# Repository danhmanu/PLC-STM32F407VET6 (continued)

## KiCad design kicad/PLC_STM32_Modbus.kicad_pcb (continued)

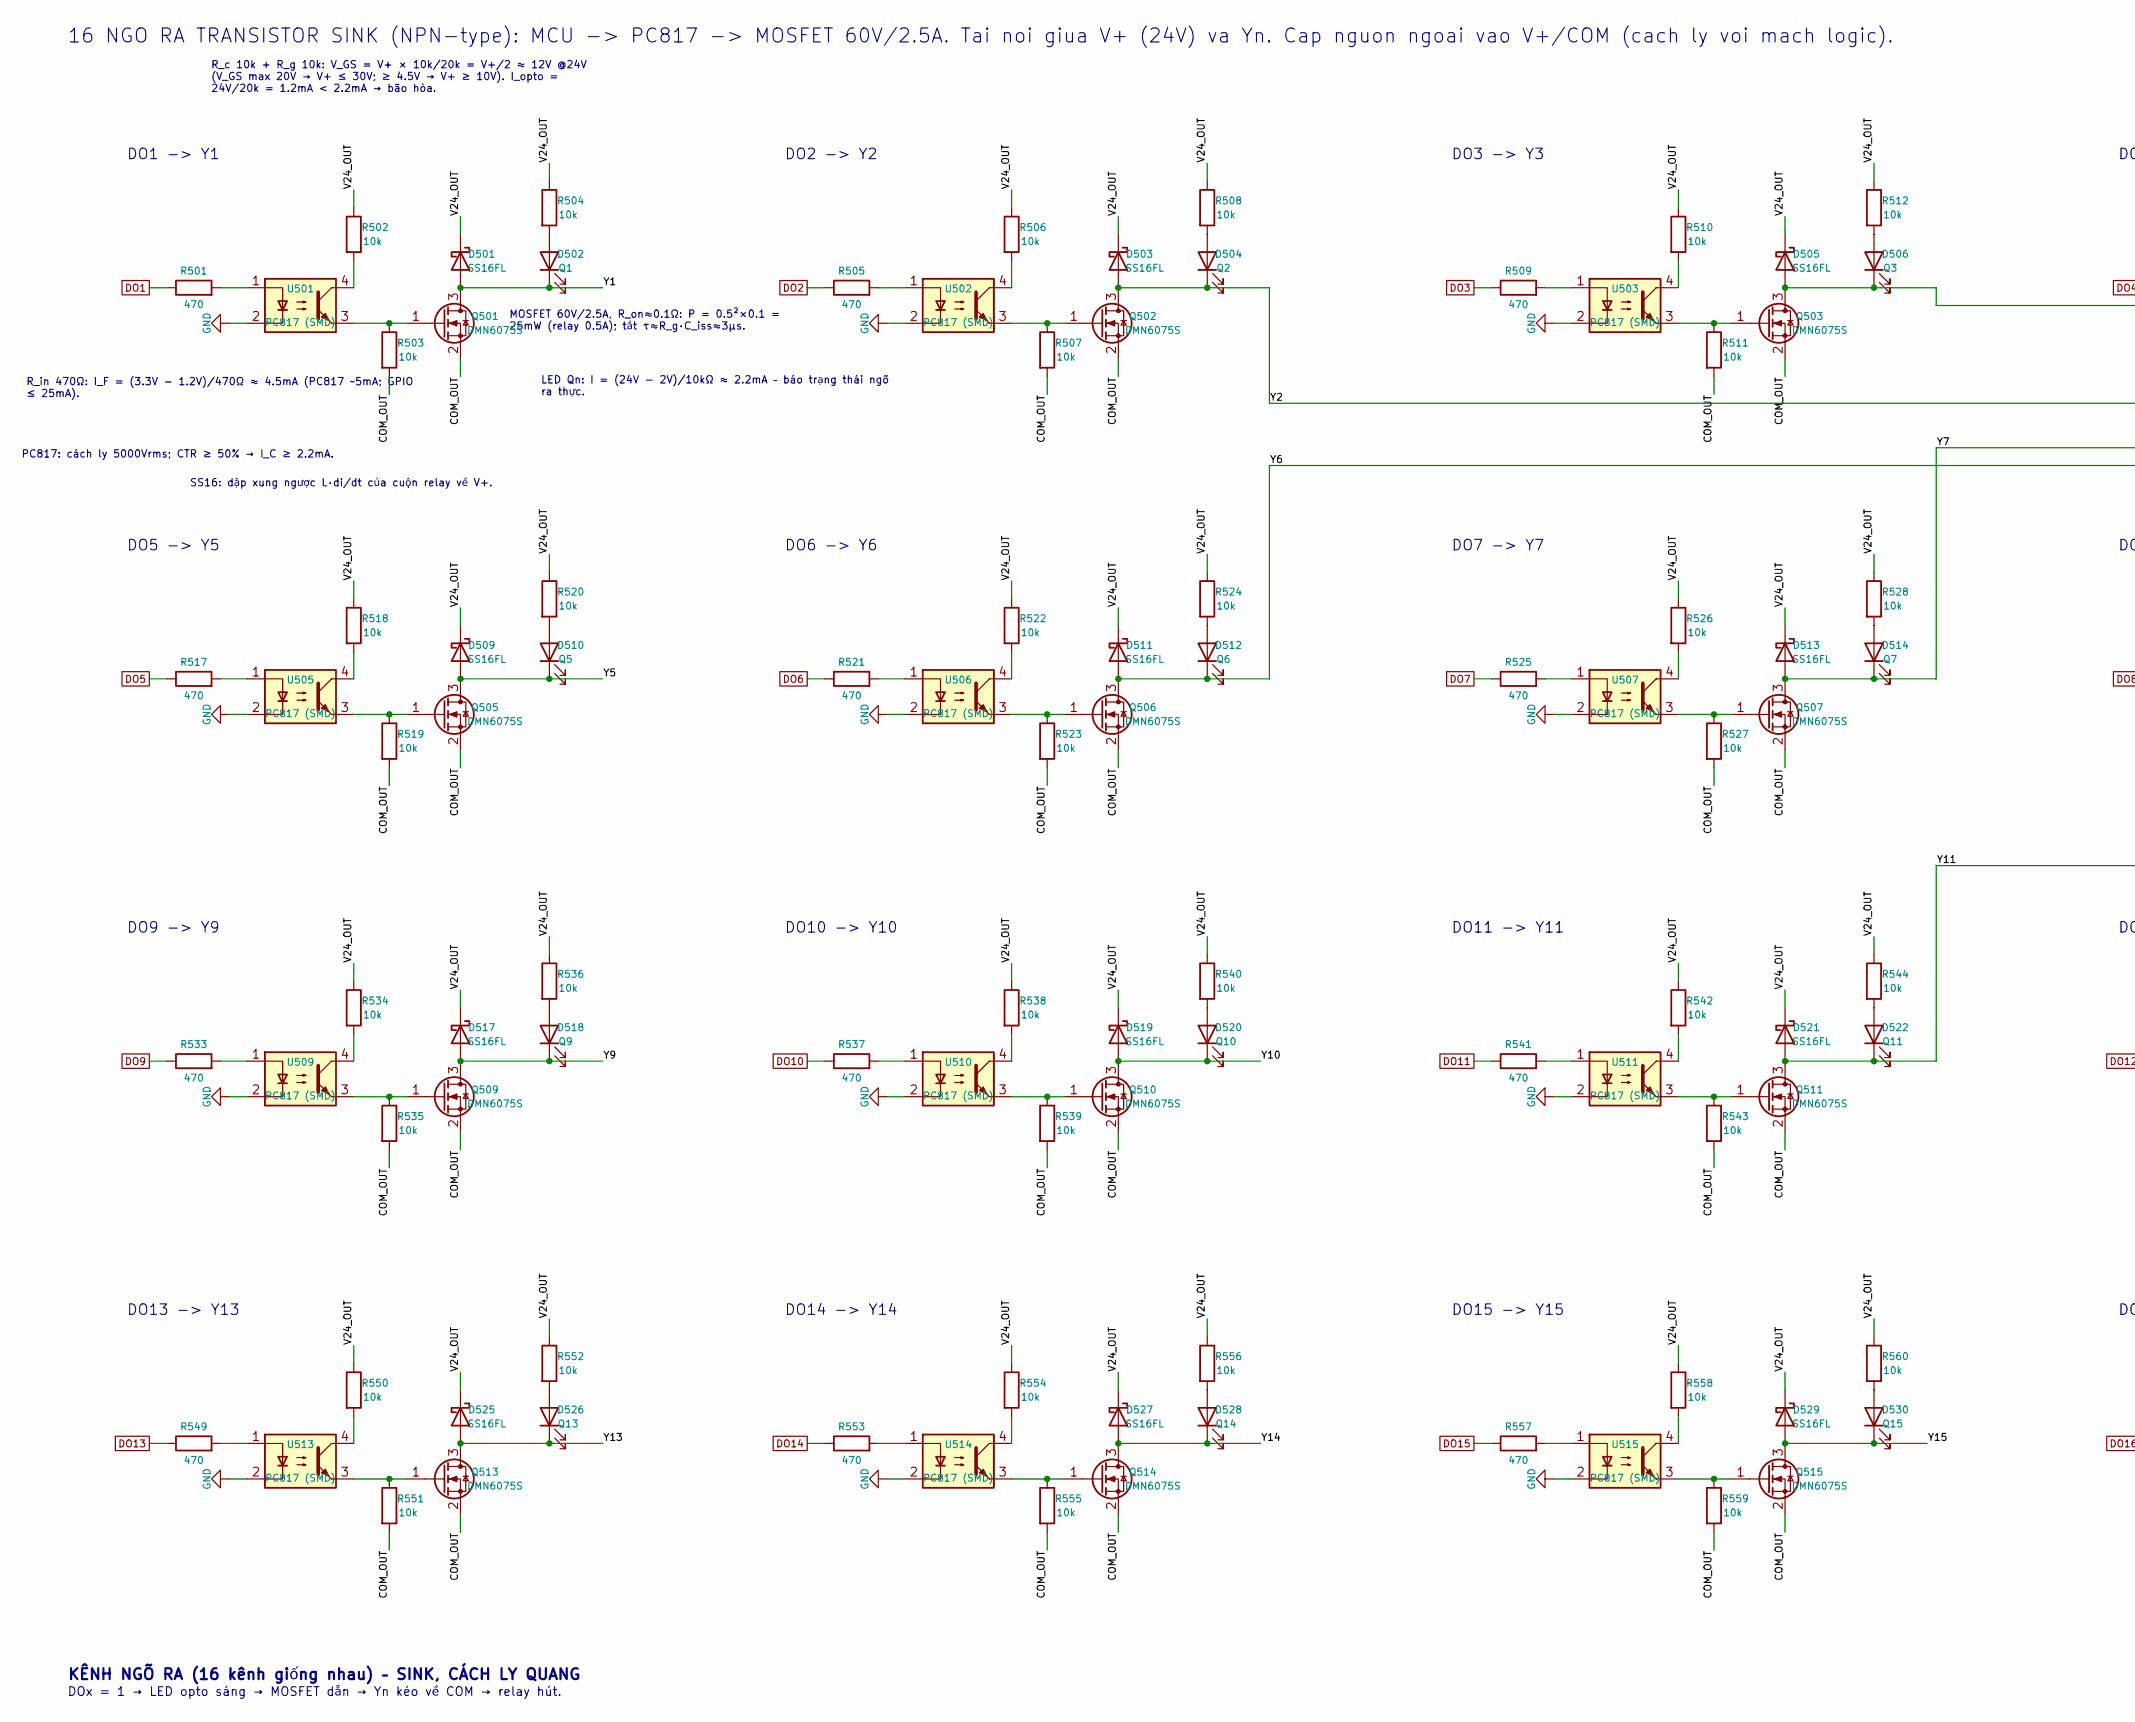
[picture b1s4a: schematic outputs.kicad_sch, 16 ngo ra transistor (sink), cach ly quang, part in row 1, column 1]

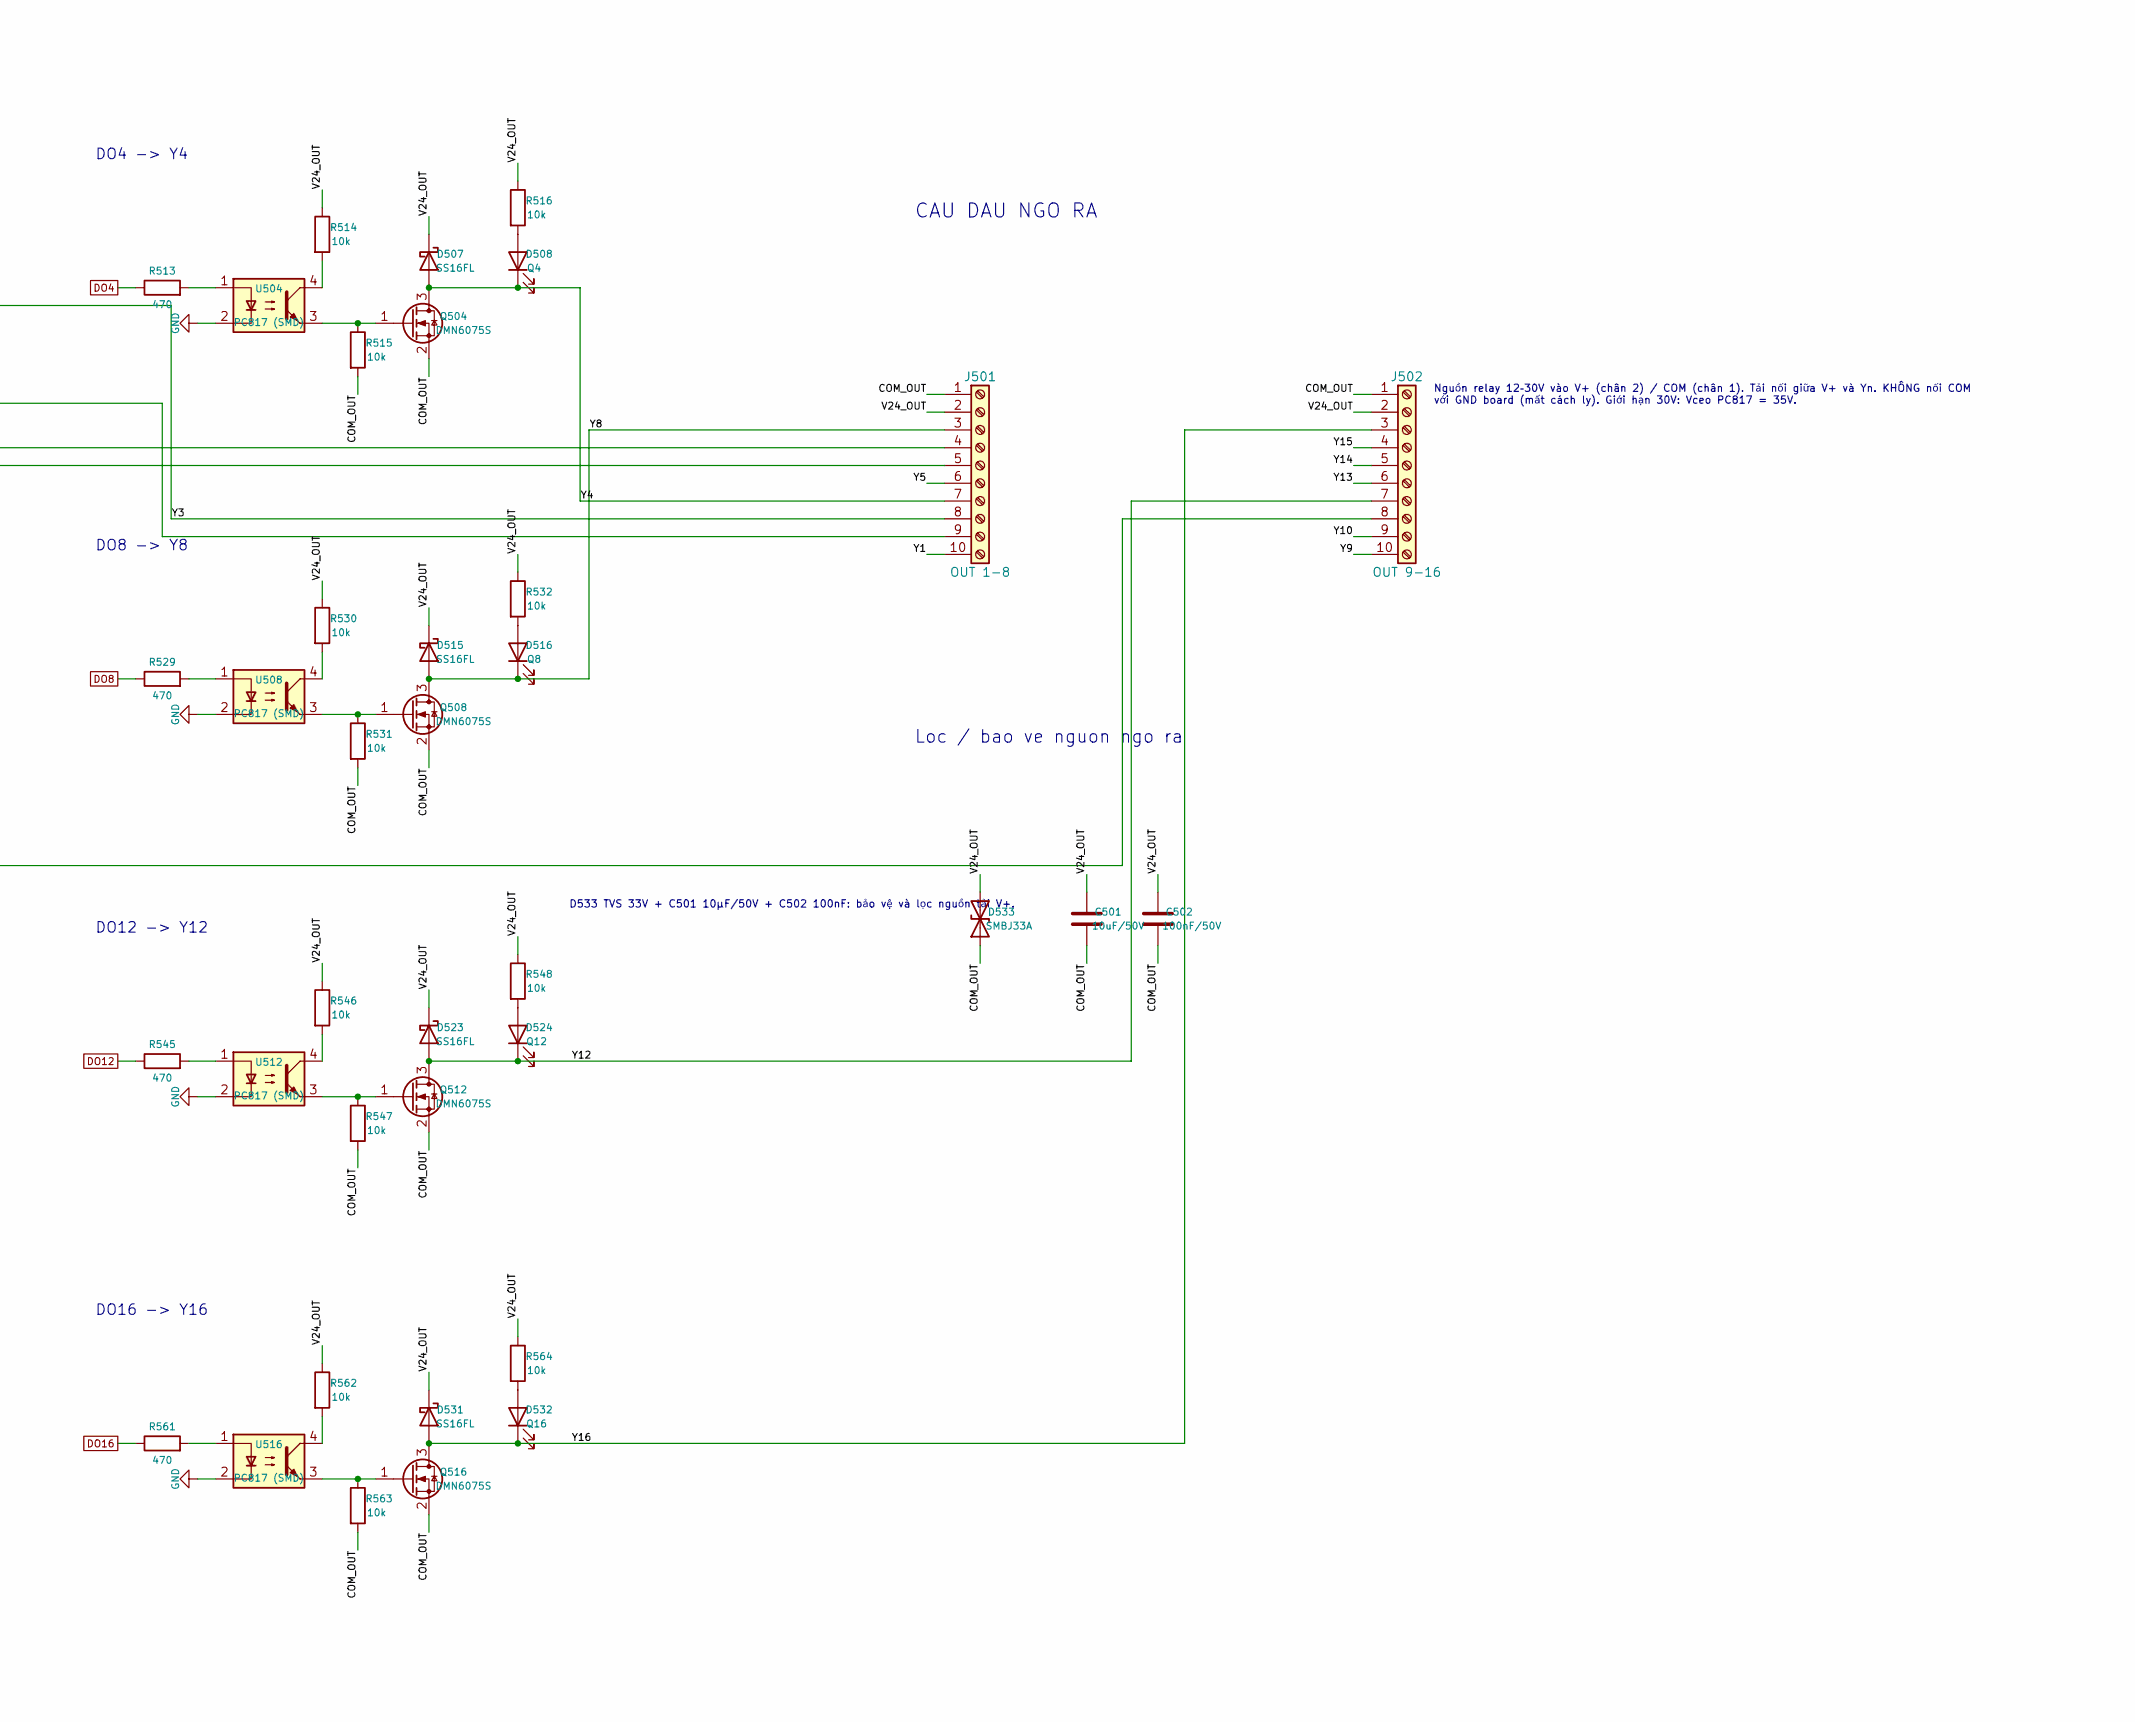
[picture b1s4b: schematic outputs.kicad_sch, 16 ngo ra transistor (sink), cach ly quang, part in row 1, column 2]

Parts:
C501: 10uF/50V; C_1206_3216Metric
C502: 100nF/50V; C_0805_2012Metric
D501, D503, D505, D507, D509, D511, D513, D515, D517, D519, D521, D523, D525, D527, D529, D531: SS16FL; D_SOD-123F
D502: Q1; LED_0603_1608Metric
D504: Q2; LED_0603_1608Metric
D506: Q3; LED_0603_1608Metric
D508: Q4; LED_0603_1608Metric
D510: Q5; LED_0603_1608Metric
D512: Q6; LED_0603_1608Metric
D514: Q7; LED_0603_1608Metric
D516: Q8; LED_0603_1608Metric
D518: Q9; LED_0603_1608Metric
D520: Q10; LED_0603_1608Metric
D522: Q11; LED_0603_1608Metric
D524: Q12; LED_0603_1608Metric
D526: Q13; LED_0603_1608Metric
D528: Q14; LED_0603_1608Metric
D530: Q15; LED_0603_1608Metric
D532: Q16; LED_0603_1608Metric
D533: SMBJ33A; D_SMB
J501: OUT 1-8; TerminalBlock_Phoenix_MKDS-1-10-3.81_1x10_P3.81mm_Horizontal
J502: OUT 9-16; TerminalBlock_Phoenix_MKDS-1-10-3.81_1x10_P3.81mm_Horizontal
Q501, Q502, Q503, Q504, Q505, Q506, Q507, Q508, Q509, Q510, Q511, Q512, Q513, Q514, Q515, Q516: DMN6075S; SOT-23
R501, R505, R509, R513, R517, R521, R525, R529, R533, R537, R541, R545, R549, R553, R557, R561: 470; R_0603_1608Metric
R502, R503, R504, R506, R507, R508, R510, R511, R512, R514, R515, R516, R518, R519, R520, R522, R523, R524, R526, R527, R528, R530, R531, R532, R534, R535, R536, R538, R539, R540, R542, R543, R544, R546, R547, R548, R550, R551, R552, R554, R555, R556, R558, R559, R560, R562, R563, R564: 10k; R_0603_1608Metric
U501, U502, U503, U504, U505, U506, U507, U508, U509, U510, U511, U512, U513, U514, U515, U516: PC817 (SMD); SMDIP-4_W9.53mm

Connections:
/16 ngo ra transistor/COM_OUT: C501.2, C502.2, D533.1 (A1), J501.1, J502.1, Q501.2 (S), Q502.2 (S), Q503.2 (S), Q504.2 (S), Q505.2 (S), Q506.2 (S), Q507.2 (S), Q508.2 (S), Q509.2 (S), Q510.2 (S), Q511.2 (S), Q512.2 (S), Q513.2 (S), Q514.2 (S), Q515.2 (S), Q516.2 (S), R503.2, R507.2, R511.2, R515.2, R519.2, R523.2, R527.2, R531.2, R535.2, R539.2, R543.2, R547.2, R551.2, R555.2, R559.2, R563.2
/16 ngo ra transistor/V24_OUT: C501.1, C502.1, D501.1 (K), D503.1 (K), D505.1 (K), D507.1 (K), D509.1 (K), D511.1 (K), D513.1 (K), D515.1 (K), D517.1 (K), D519.1 (K), D521.1 (K), D523.1 (K), D525.1 (K), D527.1 (K), D529.1 (K), D531.1 (K), D533.2 (A2), J501.2, J502.2, R502.1, R504.1, R506.1, R508.1, R510.1, R512.1, R514.1, R516.1, R518.1, R520.1, R522.1, R524.1, R526.1, R528.1, R530.1, R532.1, R534.1, R536.1, R538.1, R540.1, R542.1, R544.1, R546.1, R548.1, R550.1, R552.1, R554.1, R556.1, R558.1, R560.1, R562.1, R564.1
/16 ngo ra transistor/Y1: D501.2 (A), D502.1 (K), J501.10, Q501.3 (D)
/16 ngo ra transistor/Y2: D503.2 (A), D504.1 (K), J501.9, Q502.3 (D)
/16 ngo ra transistor/Y3: D505.2 (A), D506.1 (K), J501.8, Q503.3 (D)
/16 ngo ra transistor/Y4: D507.2 (A), D508.1 (K), J501.7, Q504.3 (D)
/16 ngo ra transistor/Y5: D509.2 (A), D510.1 (K), J501.6, Q505.3 (D)
/16 ngo ra transistor/Y6: D511.2 (A), D512.1 (K), J501.5, Q506.3 (D)
/16 ngo ra transistor/Y7: D513.2 (A), D514.1 (K), J501.4, Q507.3 (D)
/16 ngo ra transistor/Y8: D515.2 (A), D516.1 (K), J501.3, Q508.3 (D)
/16 ngo ra transistor/Y9: D517.2 (A), D518.1 (K), J502.10, Q509.3 (D)
/16 ngo ra transistor/Y10: D519.2 (A), D520.1 (K), J502.9, Q510.3 (D)
/16 ngo ra transistor/Y11: D521.2 (A), D522.1 (K), J502.8, Q511.3 (D)
/16 ngo ra transistor/Y12: D523.2 (A), D524.1 (K), J502.7, Q512.3 (D)
/16 ngo ra transistor/Y13: D525.2 (A), D526.1 (K), J502.6, Q513.3 (D)
/16 ngo ra transistor/Y14: D527.2 (A), D528.1 (K), J502.5, Q514.3 (D)
/16 ngo ra transistor/Y15: D529.2 (A), D530.1 (K), J502.4, Q515.3 (D)
/16 ngo ra transistor/Y16: D531.2 (A), D532.1 (K), J502.3, Q516.3 (D)
DO1: R501.1; also elsewhere on the board
DO2: R505.1; also elsewhere on the board
DO3: R509.1; also elsewhere on the board
DO4: R513.1; also elsewhere on the board
DO5: R517.1; also elsewhere on the board
DO6: R521.1; also elsewhere on the board
DO7: R525.1; also elsewhere on the board
DO8: R529.1; also elsewhere on the board
DO9: R533.1; also elsewhere on the board
DO10: R537.1; also elsewhere on the board
DO11: R541.1; also elsewhere on the board
DO12: R545.1; also elsewhere on the board
DO13: R549.1; also elsewhere on the board
DO14: R553.1; also elsewhere on the board
DO15: R557.1; also elsewhere on the board
DO16: R561.1; also elsewhere on the board
GND: U501.2, U502.2, U503.2, U504.2, U505.2, U506.2, U507.2, U508.2, U509.2, U510.2, U511.2, U512.2, U513.2, U514.2, U515.2, U516.2; also elsewhere on the board
unnamed: D502.2 (A), R504.2
unnamed: D504.2 (A), R508.2
unnamed: D506.2 (A), R512.2
unnamed: D508.2 (A), R516.2
unnamed: D510.2 (A), R520.2
unnamed: D512.2 (A), R524.2
unnamed: D514.2 (A), R528.2
unnamed: D516.2 (A), R532.2
unnamed: D518.2 (A), R536.2
unnamed: D520.2 (A), R540.2
unnamed: D522.2 (A), R544.2
unnamed: D524.2 (A), R548.2
unnamed: D526.2 (A), R552.2
unnamed: D528.2 (A), R556.2
unnamed: D530.2 (A), R560.2
unnamed: D532.2 (A), R564.2
unnamed: Q501.1 (G), R503.1, U501.3
unnamed: Q502.1 (G), R507.1, U502.3
unnamed: Q503.1 (G), R511.1, U503.3
unnamed: Q504.1 (G), R515.1, U504.3
unnamed: Q505.1 (G), R519.1, U505.3
unnamed: Q506.1 (G), R523.1, U506.3
unnamed: Q507.1 (G), R527.1, U507.3
unnamed: Q508.1 (G), R531.1, U508.3
unnamed: Q509.1 (G), R535.1, U509.3
unnamed: Q510.1 (G), R539.1, U510.3
unnamed: Q511.1 (G), R543.1, U511.3
unnamed: Q512.1 (G), R547.1, U512.3
unnamed: Q513.1 (G), R551.1, U513.3
unnamed: Q514.1 (G), R555.1, U514.3
unnamed: Q515.1 (G), R559.1, U515.3
unnamed: Q516.1 (G), R563.1, U516.3
unnamed: R501.2, U501.1
unnamed: R502.2, U501.4
unnamed: R505.2, U502.1
unnamed: R506.2, U502.4
unnamed: R509.2, U503.1
unnamed: R510.2, U503.4
unnamed: R513.2, U504.1
unnamed: R514.2, U504.4
unnamed: R517.2, U505.1
unnamed: R518.2, U505.4
unnamed: R521.2, U506.1
unnamed: R522.2, U506.4
unnamed: R525.2, U507.1
unnamed: R526.2, U507.4
unnamed: R529.2, U508.1
unnamed: R530.2, U508.4
unnamed: R533.2, U509.1
unnamed: R534.2, U509.4
unnamed: R537.2, U510.1
unnamed: R538.2, U510.4
unnamed: R541.2, U511.1
unnamed: R542.2, U511.4
unnamed: R545.2, U512.1
unnamed: R546.2, U512.4
unnamed: R549.2, U513.1
unnamed: R550.2, U513.4
unnamed: R553.2, U514.1
unnamed: R554.2, U514.4
unnamed: R557.2, U515.1
unnamed: R558.2, U515.4
unnamed: R561.2, U516.1
unnamed: R562.2, U516.4

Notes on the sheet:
DO14 -> Y14
DO4 -> Y4
PC817: cách ly 5000Vrms; CTR ≥ 50% → I_C ≥ 2.2mA.
D533 TVS 33V + C501 10µF/50V + C502 100nF: bảo vệ và lọc nguồn tải V+.
KÊNH NGÕ RA (16 kênh giống nhau) – SINK, CÁCH LY QUANG
DO9 -> Y9
DO3 -> Y3
DO1 -> Y1
LED Qn: I = (24V − 2V)/10kΩ ≈ 2.2mA – báo trạng thái ngõ ra thực.
DO5 -> Y5
DO12 -> Y12
Nguồn relay 12–30V vào V+ (chân 2) / COM (chân 1). Tải nối giữa V+ và Yn. KHÔNG nối COM với GND board (mất cách ly). Giới hạn 30V: Vceo PC817 = 35V.
R_c 10k + R_g 10k: V_GS = V+ × 10k/20k = V+/2 ≈ 12V @24V (V_GS max 20V → V+ ≤ 30V; ≥ 4.5V → V+ ≥ 10V). I_opto = 24V/20k = 1.2mA < 2.2mA → bão hòa.
DO6 -> Y6
16 NGO RA TRANSISTOR SINK (NPN-type): MCU -> PC817 -> MOSFET 60V/2.5A. Tai noi giua V+ (24V) va Yn. Cap nguon ngoai vao V+/COM (cach ly voi mach logic).
MOSFET 60V/2.5A, R_on≈0.1Ω: P = 0.5²×0.1 = 25mW (relay 0.5A); tắt τ≈R_g·C_iss≈3µs.
DO13 -> Y13
CAU DAU NGO RA
DO16 -> Y16
DO10 -> Y10
R_in 470Ω: I_F = (3.3V − 1.2V)/470Ω ≈ 4.5mA (PC817 ~5mA; GPIO ≤ 25mA).
DO7 -> Y7
DO2 -> Y2
DO11 -> Y11
DO8 -> Y8
DOx = 1 → LED opto sáng → MOSFET dẫn → Yn kéo về COM → relay hút.
Loc / bao ve nguon ngo ra
DO15 -> Y15
SS16: dập xung ngược L·di/dt của cuộn relay về V+.

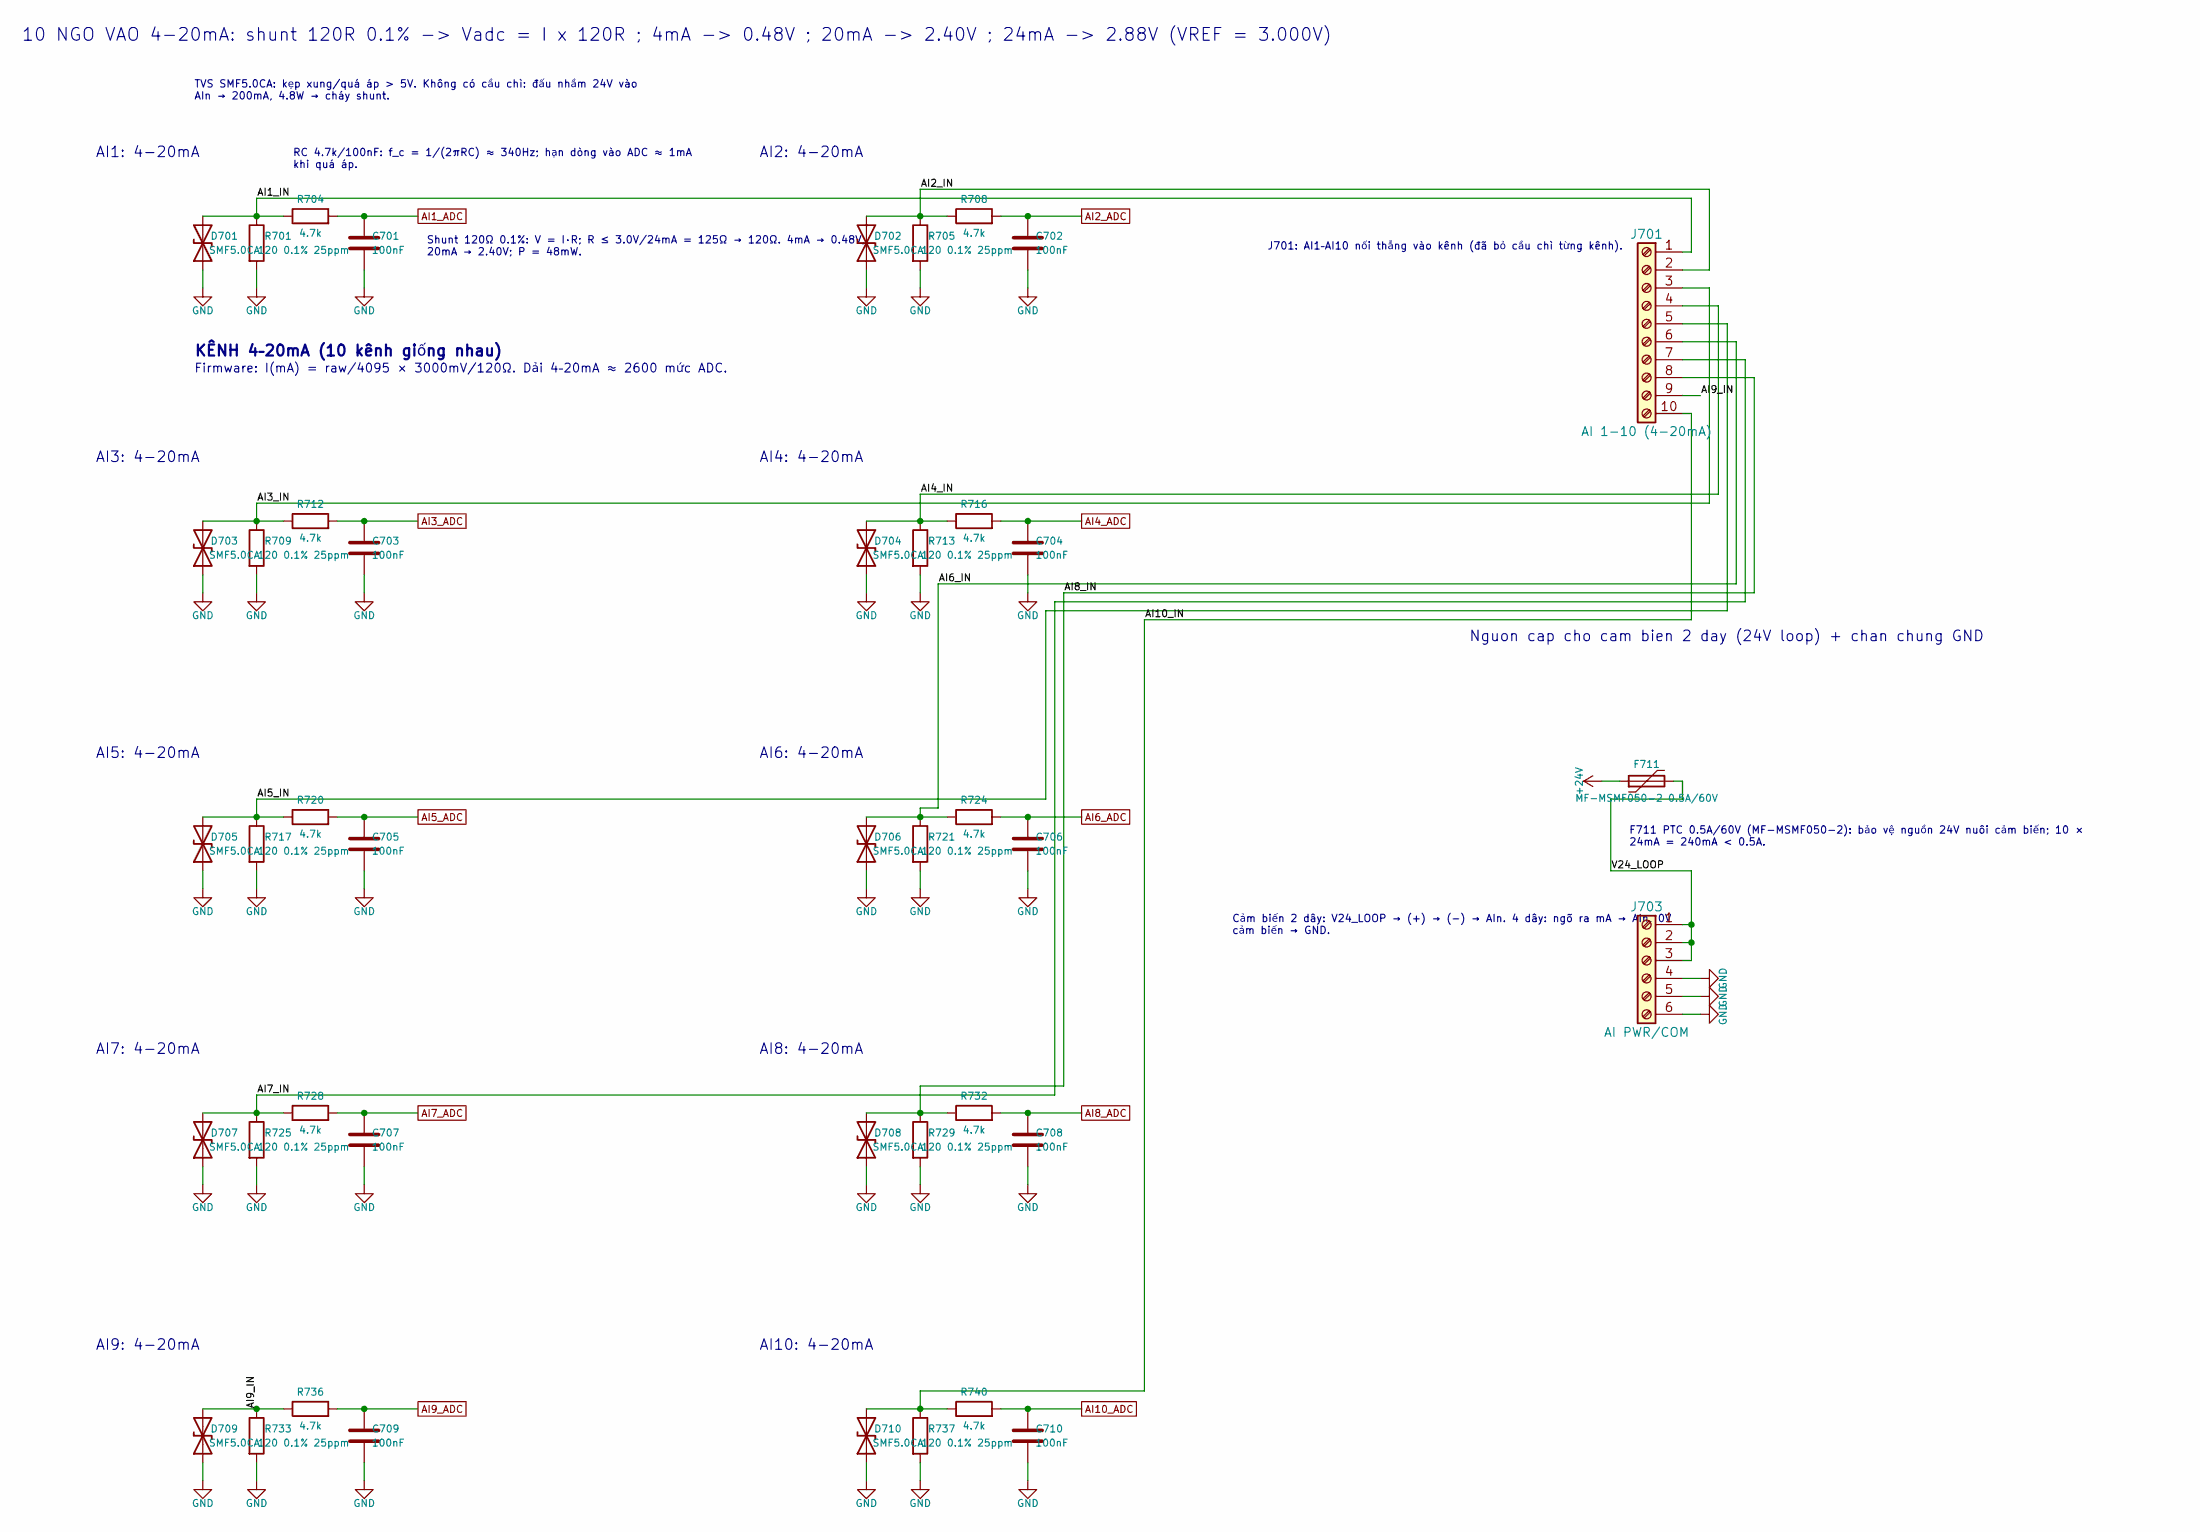
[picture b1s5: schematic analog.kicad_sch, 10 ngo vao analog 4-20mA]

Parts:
C701, C702, C703, C704, C705, C706, C707, C708, C709, C710: 100nF; C_0603_1608Metric
D701, D702, D703, D704, D705, D706, D707, D708, D709, D710: SMF5.0CA; D_SOD-123F
F711: MF-MSMF050-2 0.5A/60V; Fuse_1812_4532Metric
J701: AI 1-10 (4-20mA); TerminalBlock_Phoenix_MKDS-1-10-3.81_1x10_P3.81mm_Horizontal
J703: AI PWR/COM; TerminalBlock_Phoenix_MKDS-1-6-3.81_1x06_P3.81mm_Horizontal
R701, R705, R709, R713, R717, R721, R725, R729, R733, R737: 120 0.1% 25ppm; R_1206_3216Metric
R704, R708, R712, R716, R720, R724, R728, R732, R736, R740: 4.7k; R_0603_1608Metric

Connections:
+24V: F711.1; also elsewhere on the board
/10 ngo vao analog/AI1_IN: D701.2 (A2), J701.1, R701.1, R704.1
/10 ngo vao analog/AI2_IN: D702.2 (A2), J701.2, R705.1, R708.1
/10 ngo vao analog/AI3_IN: D703.2 (A2), J701.3, R709.1, R712.1
/10 ngo vao analog/AI4_IN: D704.2 (A2), J701.4, R713.1, R716.1
/10 ngo vao analog/AI5_IN: D705.2 (A2), J701.5, R717.1, R720.1
/10 ngo vao analog/AI6_IN: D706.2 (A2), J701.6, R721.1, R724.1
/10 ngo vao analog/AI7_IN: D707.2 (A2), J701.7, R725.1, R728.1
/10 ngo vao analog/AI8_IN: D708.2 (A2), J701.8, R729.1, R732.1
/10 ngo vao analog/AI9_IN: D709.2 (A2), J701.9, R733.1, R736.1
/10 ngo vao analog/AI10_IN: D710.2 (A2), J701.10, R737.1, R740.1
/10 ngo vao analog/V24_LOOP: F711.2, J703.1, J703.2, J703.3
AI1_ADC: C701.1, R704.2; also elsewhere on the board
AI2_ADC: C702.1, R708.2; also elsewhere on the board
AI3_ADC: C703.1, R712.2; also elsewhere on the board
AI4_ADC: C704.1, R716.2; also elsewhere on the board
AI5_ADC: C705.1, R720.2; also elsewhere on the board
AI6_ADC: C706.1, R724.2; also elsewhere on the board
AI7_ADC: C707.1, R728.2; also elsewhere on the board
AI8_ADC: C708.1, R732.2; also elsewhere on the board
AI9_ADC: C709.1, R736.2; also elsewhere on the board
AI10_ADC: C710.1, R740.2; also elsewhere on the board
GND: C701.2, C702.2, C703.2, C704.2, C705.2, C706.2, C707.2, C708.2, C709.2, C710.2, D701.1 (A1), D702.1 (A1), D703.1 (A1), D704.1 (A1), D705.1 (A1), D706.1 (A1), D707.1 (A1), D708.1 (A1), D709.1 (A1), D710.1 (A1), J703.4, J703.5, J703.6, R701.2, R705.2, R709.2, R713.2, R717.2, R721.2, R725.2, R729.2, R733.2, R737.2; also elsewhere on the board

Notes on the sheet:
AI2: 4-20mA
AI1: 4-20mA
Cảm biến 2 dây: V24_LOOP → (+) → (−) → AIn. 4 dây: ngõ ra mA → AIn, 0V cảm biến → GND.
10 NGO VAO 4-20mA: shunt 120R 0.1% -> Vadc = I x 120R ; 4mA -> 0.48V ; 20mA -> 2.40V ; 24mA -> 2.88V (VREF = 3.000V)
KÊNH 4–20mA (10 kênh giống nhau)
F711 PTC 0.5A/60V (MF-MSMF050-2): bảo vệ nguồn 24V nuôi cảm biến; 10 × 24mA = 240mA < 0.5A.
AI9: 4-20mA
AI5: 4-20mA
AI6: 4-20mA
TVS SMF5.0CA: kẹp xung/quá áp > 5V. Không có cầu chì: đấu nhầm 24V vào AIn → 200mA, 4.8W → cháy shunt.
AI3: 4-20mA
AI7: 4-20mA
Firmware: I(mA) = raw/4095 × 3000mV/120Ω. Dải 4–20mA ≈ 2600 mức ADC.
AI10: 4-20mA
J701: AI1–AI10 nối thẳng vào kênh (đã bỏ cầu chì từng kênh).
AI8: 4-20mA
RC 4.7k/100nF: f_c = 1/(2πRC) ≈ 340Hz; hạn dòng vào ADC ≈ 1mA khi quá áp.
Shunt 120Ω 0.1%: V = I·R; R ≤ 3.0V/24mA = 125Ω → 120Ω. 4mA → 0.48V, 20mA → 2.40V; P = 48mW.
Nguon cap cho cam bien 2 day (24V loop) + chan chung GND
AI4: 4-20mA

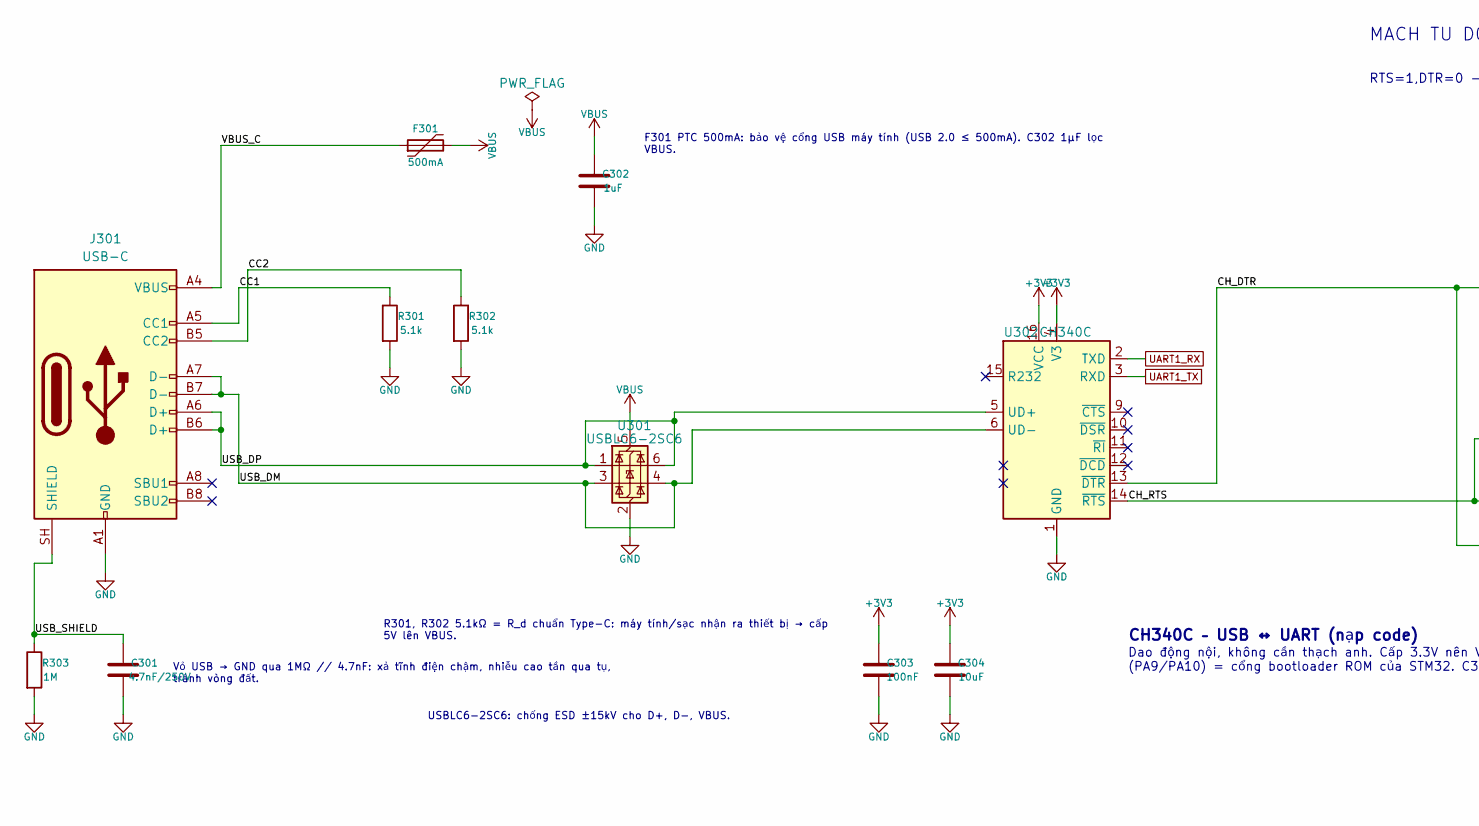
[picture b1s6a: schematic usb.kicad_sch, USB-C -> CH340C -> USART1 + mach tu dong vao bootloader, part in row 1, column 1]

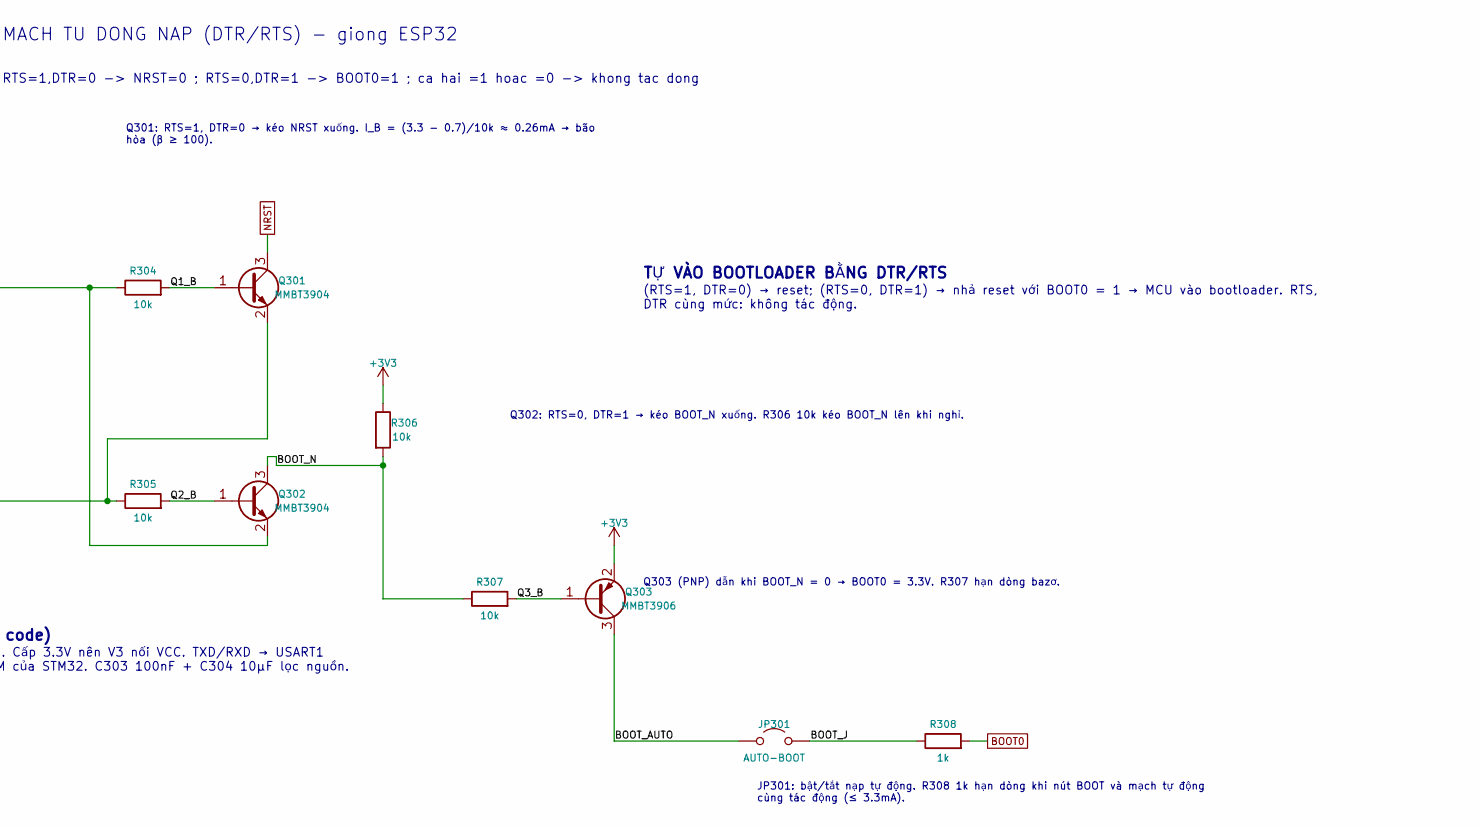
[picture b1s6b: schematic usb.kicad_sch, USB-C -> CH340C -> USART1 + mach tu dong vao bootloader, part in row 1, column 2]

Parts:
C301: 4.7nF/250V; C_1206_3216Metric
C302: 1uF; C_0603_1608Metric
C303: 100nF; C_0603_1608Metric
C304: 10uF; C_0805_2012Metric
F301: 500mA; Fuse_1206_3216Metric
J301: USB-C; USB_C_Receptacle_GCT_USB4105-xx-A_16P_TopMnt_Horizontal
JP301: AUTO-BOOT; PinHeader_1x02_P2.54mm_Vertical
Q301, Q302: MMBT3904; SOT-23
Q303: MMBT3906; SOT-23
R301, R302: 5.1k; R_0603_1608Metric
R303: 1M; R_0603_1608Metric
R304, R305, R306, R307: 10k; R_0603_1608Metric
R308: 1k; R_0603_1608Metric
U301: USBLC6-2SC6; SOT-23-6
U302: CH340C; SOIC-16_3.9x9.9mm_P1.27mm

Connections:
+3V3: C303.1, C304.1, Q303.2 (E), R306.1, U302.4 (V3), U302.16 (VCC); also elsewhere on the board
/USB nap code/BOOT_AUTO: JP301.1 (A), Q303.3 (C)
/USB nap code/BOOT_J: JP301.2 (B), R308.1
/USB nap code/BOOT_N: Q302.3 (C), R306.2, R307.1
/USB nap code/CC1: J301.A5 (CC1), R301.1
/USB nap code/CC2: J301.B5 (CC2), R302.1
/USB nap code/CH_DTR: Q302.2 (E), R304.1, U302.13 (~DTR)
/USB nap code/CH_RTS: Q301.2 (E), R305.1, U302.14 (~RTS)
/USB nap code/Q1_B: Q301.1 (B), R304.2
/USB nap code/Q2_B: Q302.1 (B), R305.2
/USB nap code/Q3_B: Q303.1 (B), R307.2
/USB nap code/USB_DM: J301.A7 (D-), J301.B7 (D-), U301.3 (I/O2), U301.4 (I/O2), U302.6 (UD-)
/USB nap code/USB_DP: J301.A6 (D+), J301.B6 (D+), U301.1 (I/O1), U301.6 (I/O1), U302.5 (UD+)
/USB nap code/USB_SHIELD: C301.1, J301.SH (SHIELD), R303.1
/USB nap code/VBUS_C: F301.1, J301.A4 (VBUS), J301.A9 (VBUS), J301.B4 (VBUS), J301.B9 (VBUS)
BOOT0: R308.2; also elsewhere on the board
GND: C301.2, C302.2, C303.2, C304.2, J301.A1 (GND), J301.A12 (GND), J301.B1 (GND), J301.B12 (GND), R301.2, R302.2, R303.2, U301.2 (GND), U302.1 (GND); also elsewhere on the board
NRST: Q301.3 (C); also elsewhere on the board
UART1_RX: U302.2 (TXD); also elsewhere on the board
UART1_TX: U302.3 (RXD); also elsewhere on the board
VBUS: C302.1, F301.2, U301.5 (VBUS); also elsewhere on the board

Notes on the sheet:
RTS=1,DTR=0 -> NRST=0 ; RTS=0,DTR=1 -> BOOT0=1 ; ca hai =1 hoac =0 -> khong tac dong
(RTS=1, DTR=0) → reset; (RTS=0, DTR=1) → nhả reset với BOOT0 = 1 → MCU vào bootloader. RTS, DTR cùng mức: không tác động.
Q302: RTS=0, DTR=1 → kéo BOOT_N xuống. R306 10k kéo BOOT_N lên khi nghỉ.
Vỏ USB → GND qua 1MΩ // 4.7nF: xả tĩnh điện chậm, nhiễu cao tần qua tụ, tránh vòng đất.
USBLC6-2SC6: chống ESD ±15kV cho D+, D−, VBUS.
Dao động nội, không cần thạch anh. Cấp 3.3V nên V3 nối VCC. TXD/RXD → USART1 (PA9/PA10) = cổng bootloader ROM của STM32. C303 100nF + C304 10µF lọc nguồn.
MACH TU DONG NAP (DTR/RTS) - giong ESP32
F301 PTC 500mA: bảo vệ cổng USB máy tính (USB 2.0 ≤ 500mA). C302 1µF lọc VBUS.
R301, R302 5.1kΩ = R_d chuẩn Type-C: máy tính/sạc nhận ra thiết bị → cấp 5V lên VBUS.
Q301: RTS=1, DTR=0 → kéo NRST xuống. I_B = (3.3 − 0.7)/10k ≈ 0.26mA → bão hòa (β ≥ 100).
JP301: bật/tắt nạp tự động. R308 1k hạn dòng khi nút BOOT và mạch tự động cùng tác động (≤ 3.3mA).
CH340C – USB ↔ UART (nạp code)
TỰ VÀO BOOTLOADER BẰNG DTR/RTS
Q303 (PNP) dẫn khi BOOT_N = 0 → BOOT0 = 3.3V. R307 hạn dòng bazơ.
